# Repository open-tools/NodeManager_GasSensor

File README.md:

MySensors AirQuality board with eight MQ gas sensors, an MH-Z19 CO2 sensor and a Plantower PMSA003 PM25 particle sensor.

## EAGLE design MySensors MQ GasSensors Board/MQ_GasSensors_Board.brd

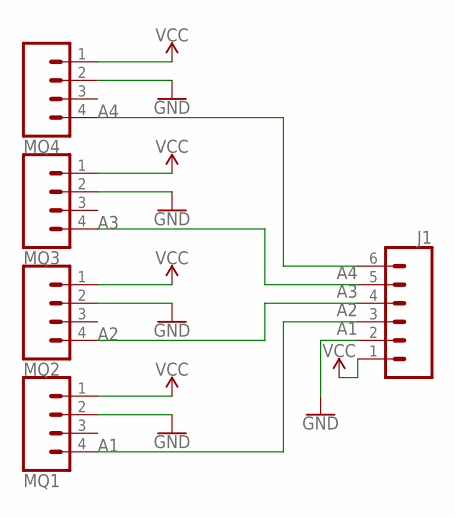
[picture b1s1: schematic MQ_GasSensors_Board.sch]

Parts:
J1: CONN_06SILK_FEMALE_PTH; 1X06
MQ1, MQ2, MQ3, MQ4: CONN_04; 1X04

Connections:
A1: J1.3, MQ1.4
A2: J1.4, MQ2.4
A3: J1.5, MQ3.4
A4: J1.6, MQ4.4
GND: J1.2, MQ1.2, MQ2.2, MQ3.2, MQ4.2
VCC: J1.1, MQ1.1, MQ2.1, MQ3.1, MQ4.1

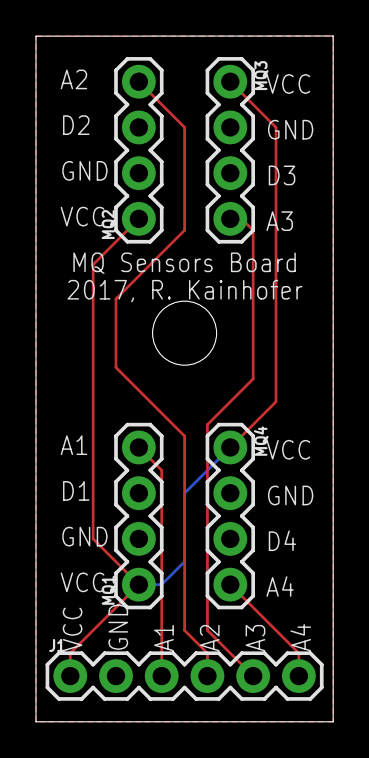
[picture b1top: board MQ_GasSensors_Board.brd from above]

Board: 2 copper layers, 16.5 x 38.1 mm, 5 parts (0 on the bottom side), 6 nets.

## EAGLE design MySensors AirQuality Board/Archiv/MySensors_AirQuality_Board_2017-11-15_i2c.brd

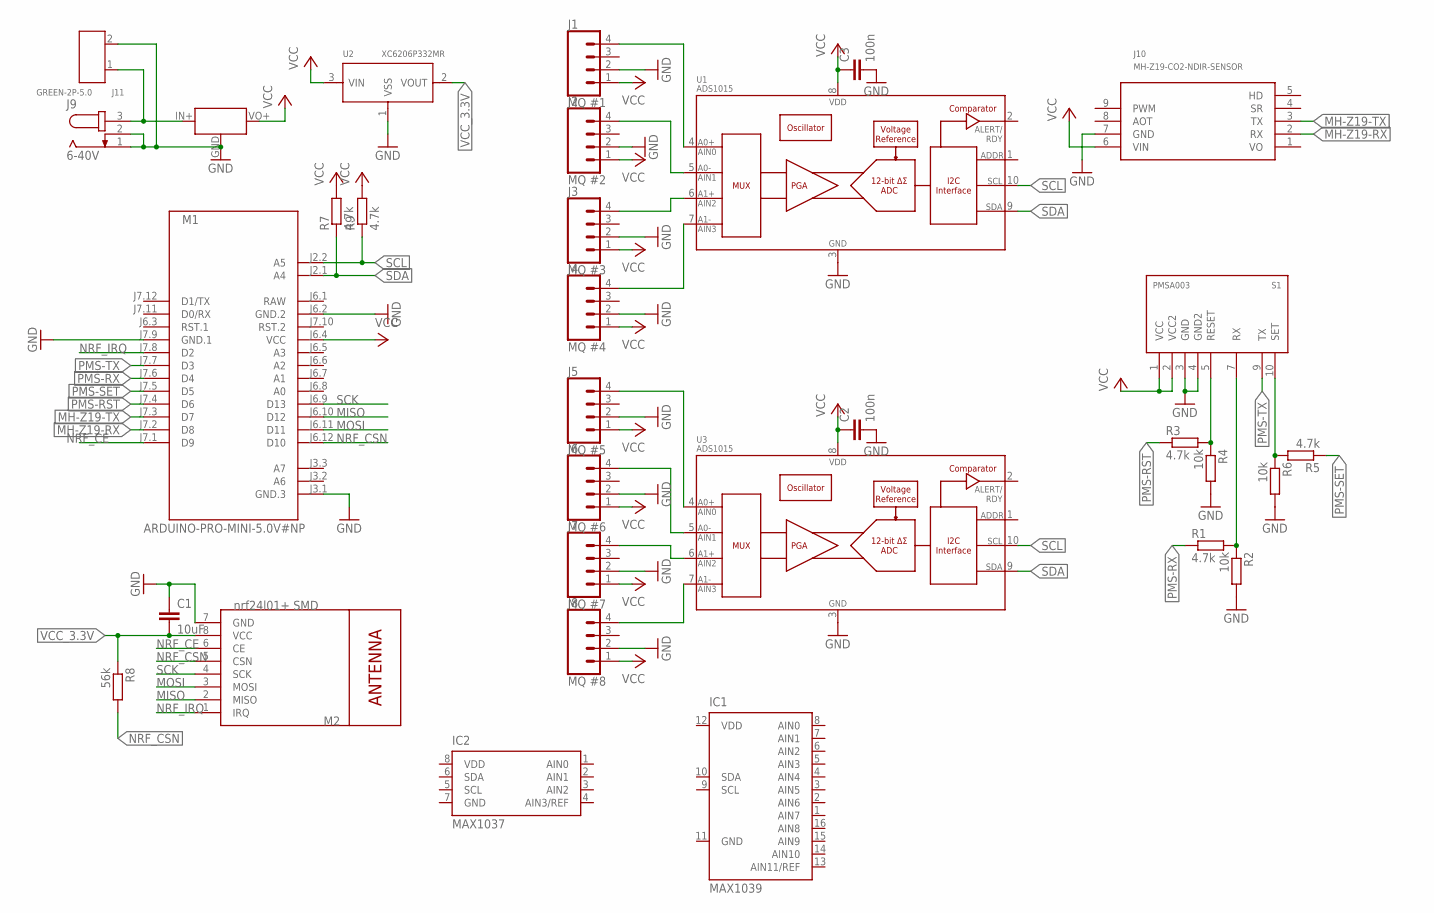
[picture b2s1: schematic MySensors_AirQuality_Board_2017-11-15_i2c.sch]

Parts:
C1: 10uF; C0805
C2, C3: 100n; C0805
IC1: MAX1039; QSOP16
IC2: MAX1037; SOT23-8L
J1: MQ #1; 1X04
J2: MQ #2; 1X04
J3: MQ #3; 1X04
J4: MQ #4; 1X04
J5: MQ #5; 1X04
J6: MQ #6; 1X04
J7: MQ #7; 1X04
J8: MQ #8; 1X04
J9: 6-40V; SPC4078
J10: MH-Z19-CO2-NDIR-SENSOR; MH-Z19
J11: GREEN-2P-5.0; H2-5.0-10.5X8.0MM
M1: ARDUINO-PRO-MINI-5.0V#NP; ARDUINO-PRO-MINI#NP
M2: nrf24l01+ SMD; WIRELESS-NRF24L01-SMD
R1, R3, R5, R7, R9: 4.7k; R0805
R2, R4, R6: 10k; R0805
R8: 56k; R0805
S1: PMSA003
U1, U3: ADS1015; MSOP10
U2: XC6206P332MR; SOT-23
U$2: MINI_BUCK_CONVERTER

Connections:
A0: J1.4, U1.4 (AIN0)
A1: J2.4, U1.5 (AIN1)
A2: J3.4, U1.6 (AIN2)
A3: J4.4, U1.7 (AIN3)
GND: C1.1, C2.2, C3.2, IC1.11 (GND), IC2.7 (GND), J1.2, J2.2, J3.2, J4.2, J5.2, J6.2, J7.2, J8.2, J9.1, J9.2, J10.7 (GND), J11.2, M1.J3.1 (GND.3), M1.J6.2 (GND.2), M1.J7.9 (GND.1), M2.7 (GND), R2.2, R4.2, R6.2, S1.3 (GND), S1.4 (GND2), U1.3 (VSS), U2.1 (VSS), U3.3 (VSS), U$2.GND
MH-Z19-RX: J10.2 (RX), M1.J7.2 (D8)
MH-Z19-TX: J10.3 (TX), M1.J7.3 (D7)
MISO: M1.J6.10 (D12), M2.2 (MISO)
MOSI: M1.J6.11 (D11), M2.3 (MOSI)
unnamed: J5.4, U3.4 (AIN0)
unnamed: J9.3, J11.1, U$2.IN+ (VIN)
unnamed: J6.4, U3.5 (AIN1)
unnamed: J7.4, U3.6 (AIN2)
unnamed: J8.4, U3.7 (AIN3)
NRF_CE: M1.J7.1 (D9), M2.6 (CE)
NRF_CSN: M1.J6.12 (D10), M2.5 (CSN), R8.2
NRF_IRQ: M1.J7.8 (D2), M2.1 (IRQ)
PMS-RESET-3.3V: R3.2, R4.1, S1.5 (RESET)
PMS-RST: M1.J7.4 (D6), R3.1
PMS-RX: M1.J7.6 (D4), R1.1
PMS-RX-3.3V: R1.2, R2.1, S1.7 (RX)
PMS-SET: M1.J7.5 (D5), R5.1
PMS-SET_3.3V: R5.2, R6.1, S1.10 (SET)
PMS-TX: M1.J7.7 (D3), S1.9 (TX)
RAW: M1.J6.1 (RAW)
SCK: M1.J6.9 (D13), M2.4 (SCK)
SCL: M1.J2.2 (A5), R9.1, U1.10 (SCL), U3.10 (SCL)
SDA: M1.J2.1 (A4), R7.1, U1.9 (SDA), U3.9 (SDA)
VCC: C2.1, C3.1, J1.1, J2.1, J3.1, J4.1, J5.1, J6.1, J7.1, J8.1, J10.6 (VIN), M1.J6.4 (VCC), R7.2, R9.2, S1.1 (VCC), S1.2 (VCC2), U1.8 (VDD), U2.3 (VIN), U3.8 (VDD), U$2.VO+ (VOUT)
VCC_3.3V: C1.2, M2.8 (VCC), R8.1, U2.2 (VOUT)
VDD: IC1.12 (VDD), IC2.8 (VDD)
VO: J10.1 (VO)

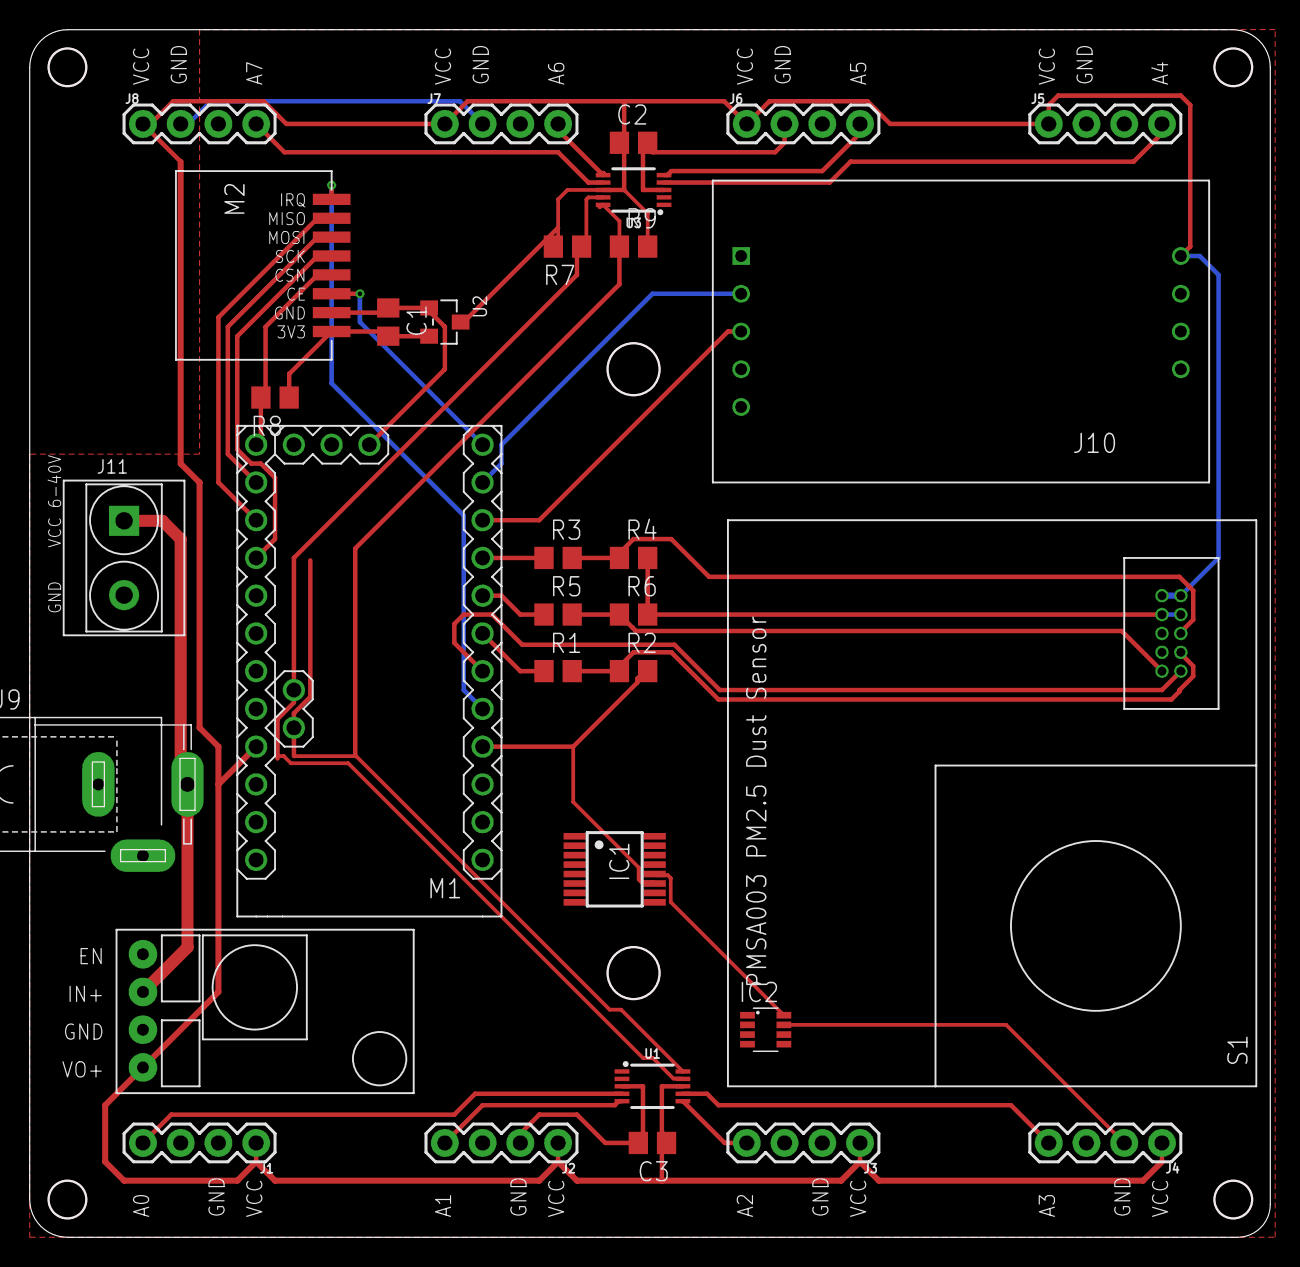
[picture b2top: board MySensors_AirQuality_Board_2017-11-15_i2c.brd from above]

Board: 2 copper layers, 83.3 x 81.1 mm, 32 parts (0 on the bottom side), 30 nets.

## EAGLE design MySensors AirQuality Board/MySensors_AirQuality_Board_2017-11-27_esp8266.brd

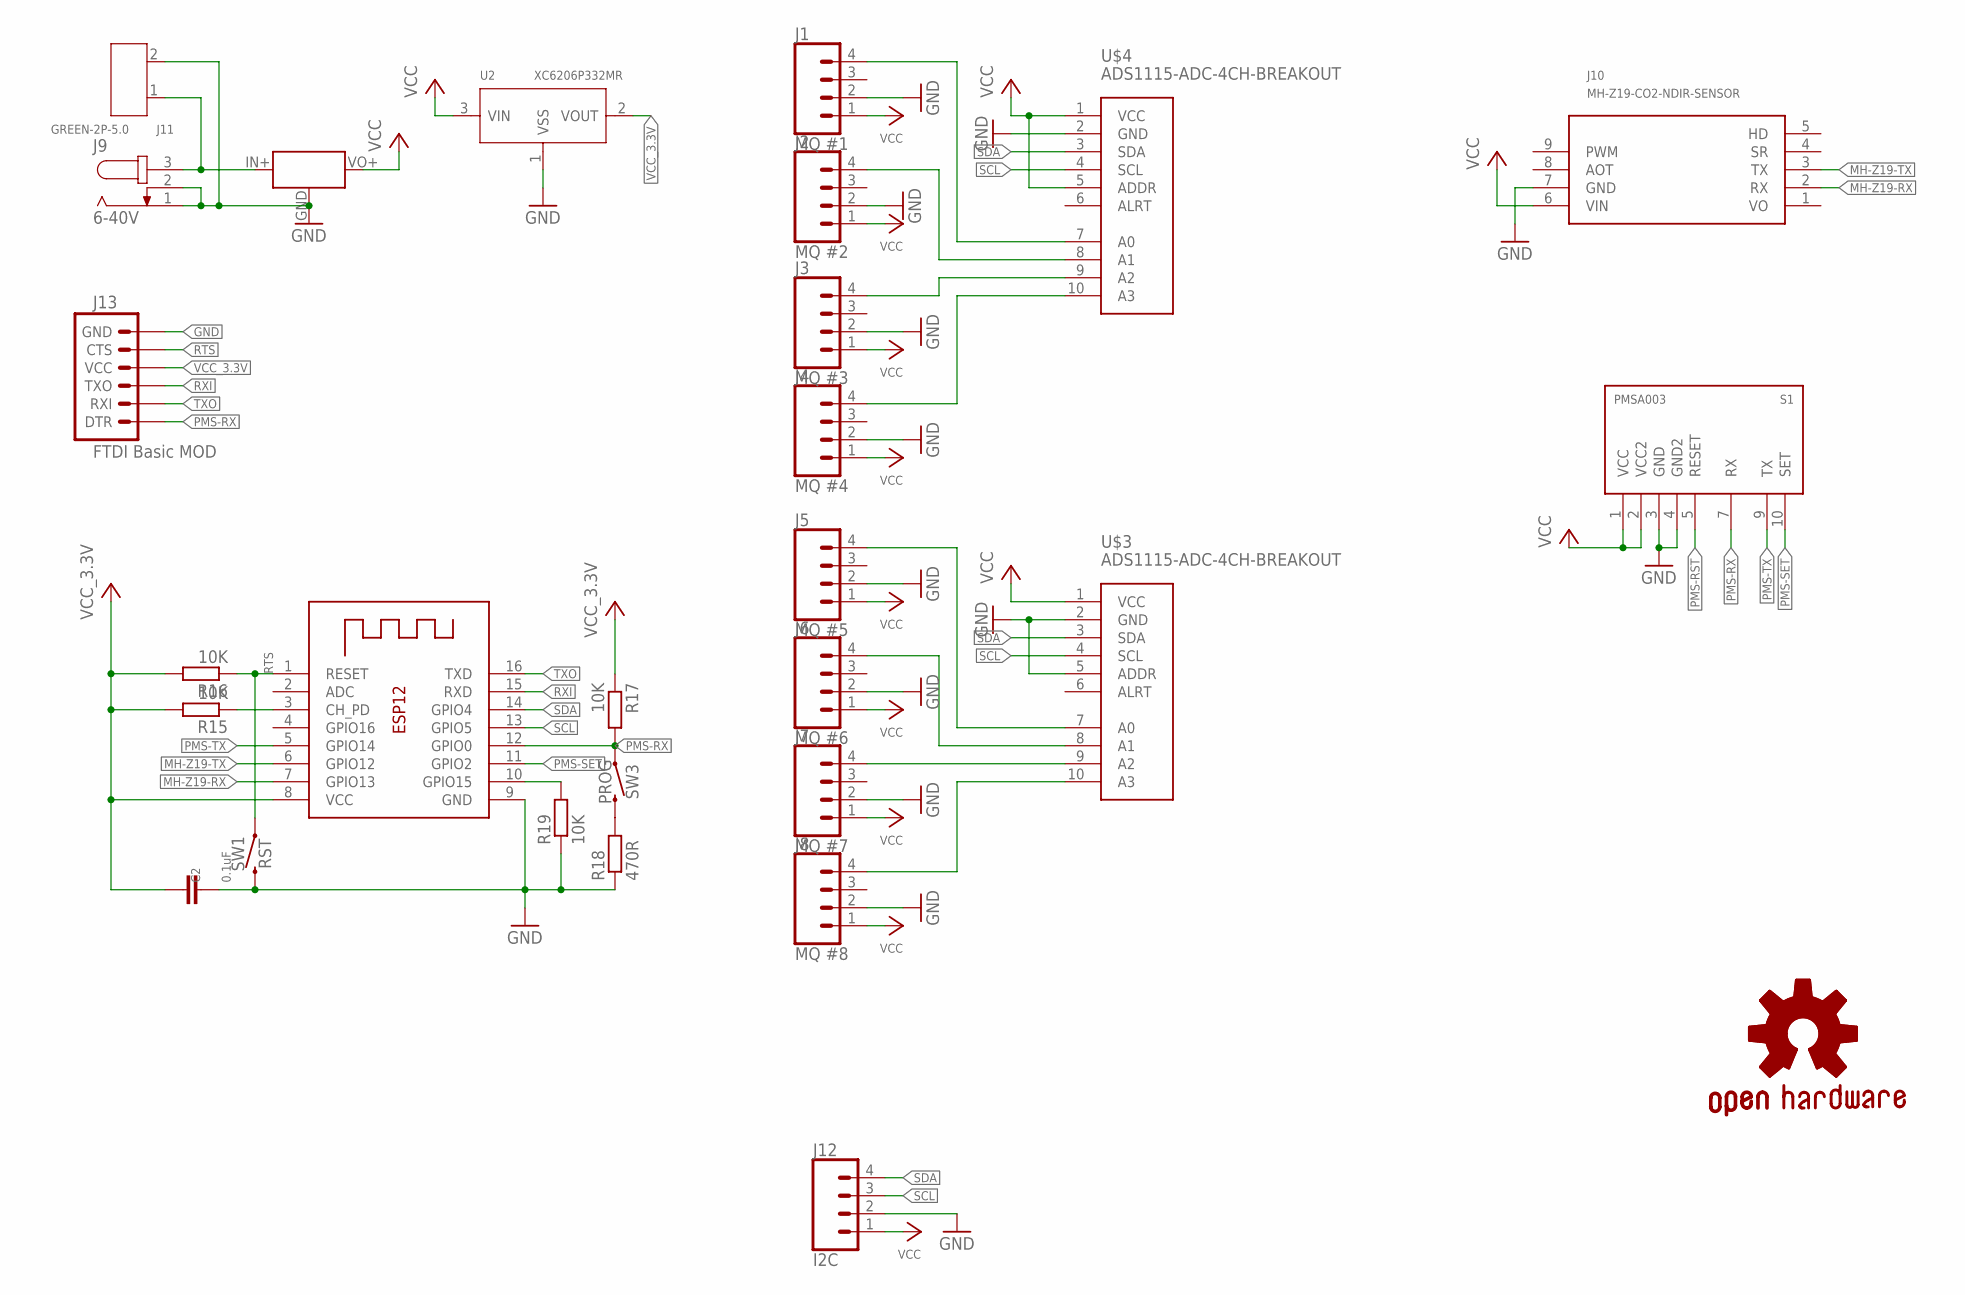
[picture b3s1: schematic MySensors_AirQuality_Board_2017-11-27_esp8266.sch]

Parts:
C2: 0.1uF; C0805
GOLD_ORB_SM1: OSHWLOGO_GOLD_ORB_SM; OSHW2
J1: MQ #1; 1X04
J2: MQ #2; 1X04
J3: MQ #3; 1X04
J4: MQ #4; 1X04
J5: MQ #5; 1X04
J6: MQ #6; 1X04
J7: MQ #7; 1X04
J8: MQ #8; 1X04
J9: 6-40V; SPC4078
J10: MH-Z19-CO2-NDIR-SENSOR; MH-Z19
J11: GREEN-2P-5.0; H2-5.0-10.5X8.0MM
J12: I2C; 1X04
J13: FTDI Basic MOD; 1X06
R15, R16, R17, R19: 10K; R0805
R18: 470R; R0805
S1: PMSA003
SW1: RST; TACTILE_SWITCH_SMD_6.0X3.5MM
SW3: PROG; TACTILE_SWITCH_SMD_6.0X3.5MM
U2: XC6206P332MR; SOT-23
U$2: MINI_BUCK_CONVERTER
U$3, U$4: ADS1115-ADC-4CH-BREAKOUT
X2: ESP-12e; ESP-12

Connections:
A0: J1.4, U$4.7 (A0)
A1: J2.4, U$4.8 (A1)
A2: J3.4, U$4.9 (A2)
A3: J4.4, U$4.10 (A3)
CH_PD: R15.1, X2.3 (CH_PD)
GND: C2.1, J1.2, J2.2, J3.2, J4.2, J5.2, J6.2, J7.2, J8.2, J9.1, J9.2, J10.7 (GND), J11.2, J12.2, J13.6 (GND), R18.1, R19.1, S1.3 (GND), S1.4 (GND2), SW1.2, U2.1 (VSS), U$2.GND, U$3.2 (GND), U$3.5 (ADDR), U$4.2 (GND), X2.9 (GND)
GPIO15: R19.2, X2.10 (GPIO15)
MH-Z19-RX: J10.2 (RX), X2.7 (GPIO13)
MH-Z19-TX: J10.3 (TX), X2.6 (GPIO12)
unnamed: J5.4, U$3.7 (A0)
unnamed: J9.3, J11.1, U$2.IN+ (VIN)
unnamed: J6.4, U$3.8 (A1)
unnamed: J7.4, U$3.9 (A2)
unnamed: J8.4, U$3.10 (A3)
unnamed: R18.2, SW3.2
PMS-RST: S1.5 (RESET)
PMS-RX: J13.1 (DTR), R17.2, S1.7 (RX), SW3.1, X2.12 (GPIO0)
PMS-SET: S1.10 (SET), X2.11 (GPIO2)
PMS-TX: S1.9 (TX), X2.5 (GPIO14)
RTS: J13.5 (CTS), R16.1, SW1.1, X2.1 (RESET)
RXI: J13.3 (TXO), X2.15 (RXD)
SCL: J12.3, U$3.4 (SCL), U$4.4 (SCL), X2.13 (GPIO5)
SDA: J12.4, U$3.3 (SDA), U$4.3 (SDA), X2.14 (GPIO4)
TXO: J13.2 (RXI), X2.16 (TXD)
VCC: J1.1, J2.1, J3.1, J4.1, J5.1, J6.1, J7.1, J8.1, J10.6 (VIN), J12.1, S1.1 (VCC), S1.2 (VCC2), U2.3 (VIN), U$2.VO+ (VOUT), U$3.1 (VCC), U$4.1 (VCC), U$4.5 (ADDR)
VCC_3.3V: C2.2, J13.4 (VCC), R15.2, R16.2, R17.1, U2.2 (VOUT), X2.8 (VCC)
VO: J10.1 (VO)

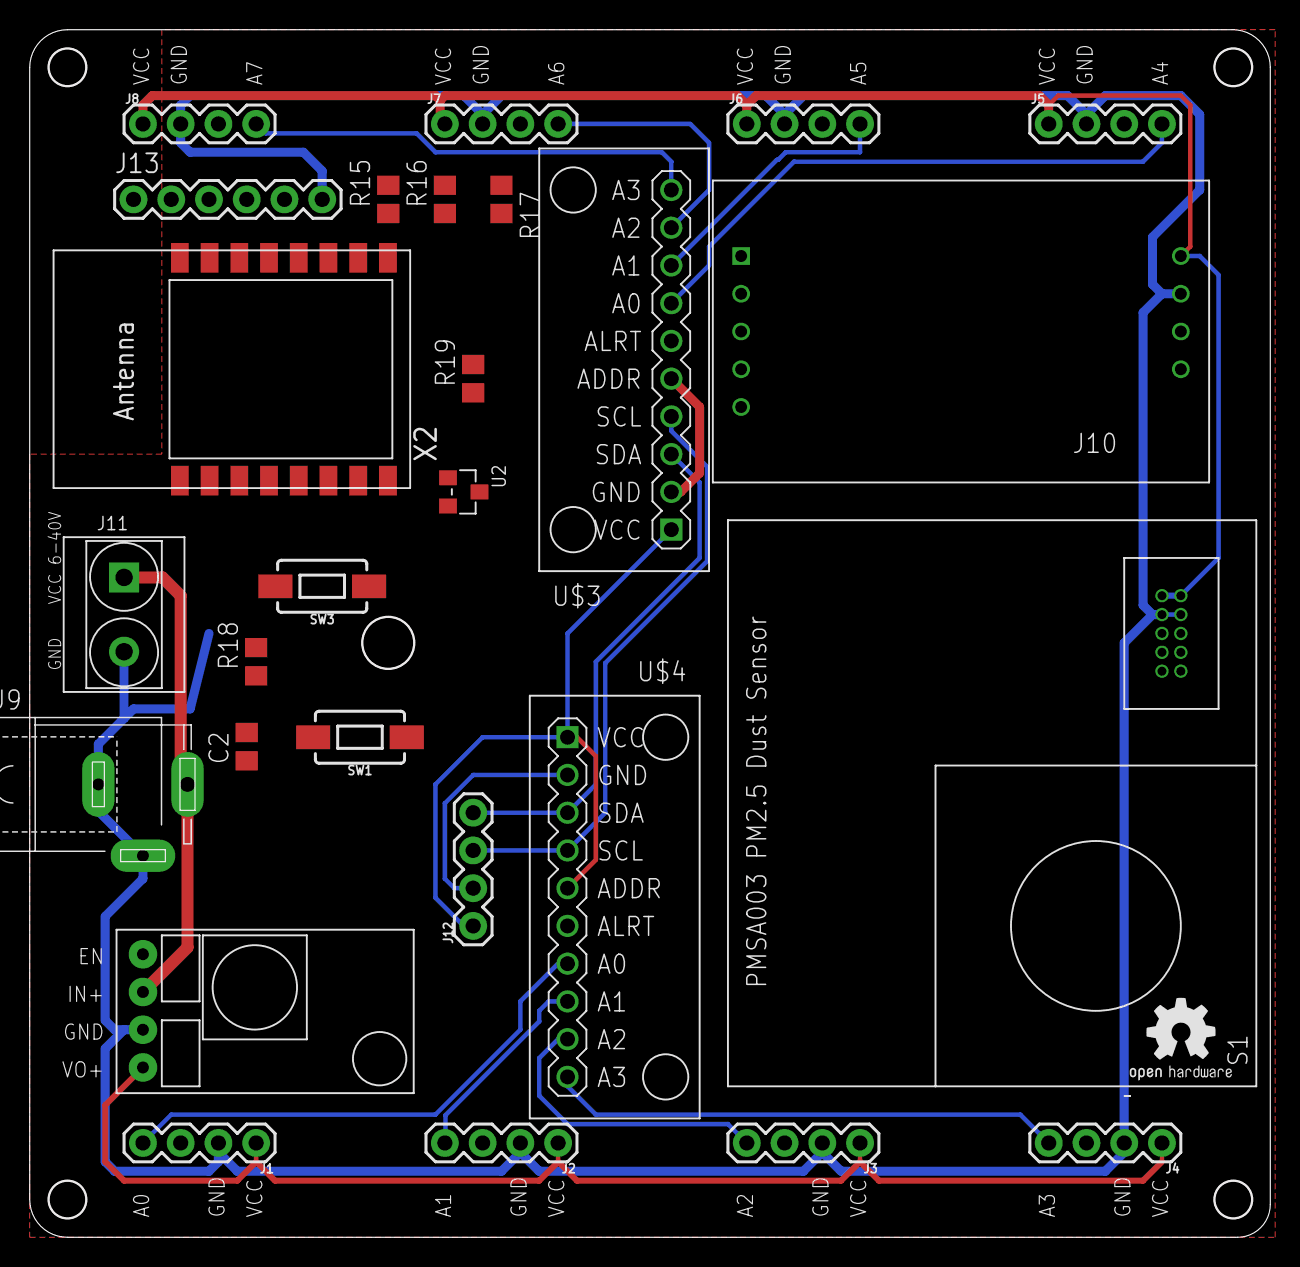
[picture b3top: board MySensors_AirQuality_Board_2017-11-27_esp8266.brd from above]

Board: 2 copper layers, 83.3 x 81.1 mm, 28 parts (0 on the bottom side), 25 nets.

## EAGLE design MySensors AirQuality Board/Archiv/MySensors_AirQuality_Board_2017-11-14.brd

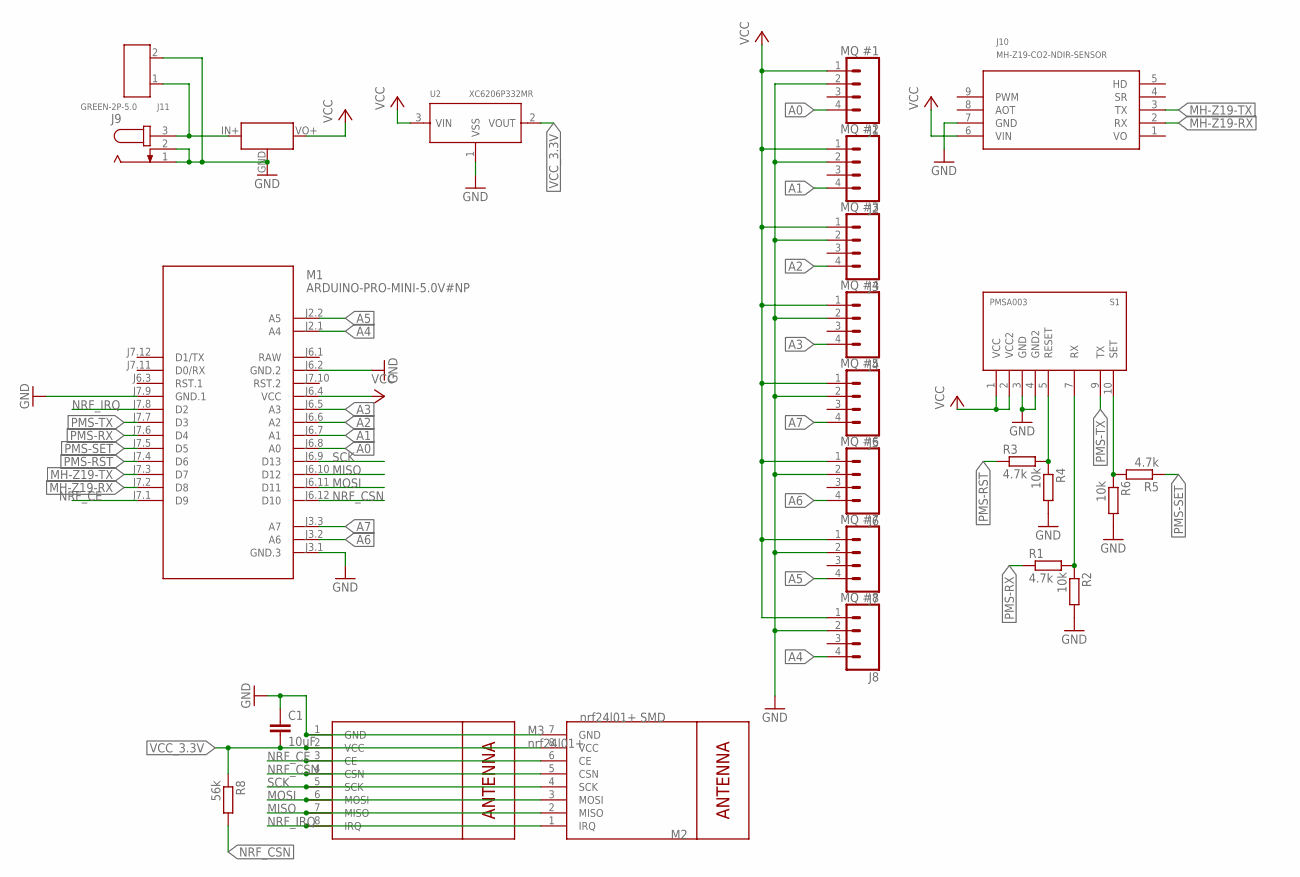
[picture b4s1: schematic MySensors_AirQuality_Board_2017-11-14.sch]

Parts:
C1: 10uF; C0805
J1: MQ #1; 1X04
J2: MQ #2; 1X04
J3: MQ #3; 1X04
J4: MQ #4; 1X04
J5: MQ #5; 1X04
J6: MQ #6; 1X04
J7: MQ #7; 1X04
J8: MQ #8; 1X04
J9: JACK-PLUG1; SPC4078
J10: MH-Z19-CO2-NDIR-SENSOR; MH-Z19
J11: GREEN-2P-5.0; H2-5.0-10.5X8.0MM
M1: ARDUINO-PRO-MINI-5.0V#NP; ARDUINO-PRO-MINI#NP
M2: nrf24l01+ SMD; WIRELESS-NRF24L01-SMD
M3: nrf24l01+; WIRELESS-NRF24L01
R1, R3, R5: 4.7k; R0805
R2, R4, R6: 10k; R0805
R8: 56k; R0805
S1: PMSA003
U2: XC6206P332MR; SOT-23
U$2: MINI_BUCK_CONVERTER

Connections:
A0: J1.4, M1.J6.8 (A0)
A1: J2.4, M1.J6.7 (A1)
A2: J3.4, M1.J6.6 (A2)
A3: J4.4, M1.J6.5 (A3)
A4: J8.4, M1.J2.1 (A4)
A5: J7.4, M1.J2.2 (A5)
A6: J6.4, M1.J3.2 (A6)
A7: J5.4, M1.J3.3 (A7)
GND: C1.1, J1.2, J2.2, J3.2, J4.2, J5.2, J6.2, J7.2, J8.2, J9.1, J9.2, J10.7 (GND), J11.2, M1.J3.1 (GND.3), M1.J6.2 (GND.2), M1.J7.9 (GND.1), M2.7 (GND), M3.1 (GND), R2.2, R4.2, R6.2, S1.3 (GND), S1.4 (GND2), U2.1 (VSS), U$2.GND
MH-Z19-RX: J10.2 (RX), M1.J7.2 (D8)
MH-Z19-TX: J10.3 (TX), M1.J7.3 (D7)
MISO: M1.J6.10 (D12), M2.2 (MISO), M3.7 (MISO)
MOSI: M1.J6.11 (D11), M2.3 (MOSI), M3.6 (MOSI)
unnamed: J9.3, J11.1, U$2.IN+ (VIN)
NRF_CE: M1.J7.1 (D9), M2.6 (CE), M3.3 (CE)
NRF_CSN: M1.J6.12 (D10), M2.5 (CSN), M3.4 (CSN), R8.2
NRF_IRQ: M1.J7.8 (D2), M2.1 (IRQ), M3.8 (IRQ)
PMS-RESET-3.3V: R3.2, R4.1, S1.5 (RESET)
PMS-RST: M1.J7.4 (D6), R3.1
PMS-RX: M1.J7.6 (D4), R1.1
PMS-RX-3.3V: R1.2, R2.1, S1.7 (RX)
PMS-SET: M1.J7.5 (D5), R5.1
PMS-SET_3.3V: R5.2, R6.1, S1.10 (SET)
PMS-TX: M1.J7.7 (D3), S1.9 (TX)
RAW: M1.J6.1 (RAW)
SCK: M1.J6.9 (D13), M2.4 (SCK), M3.5 (SCK)
VCC: J1.1, J2.1, J3.1, J4.1, J5.1, J6.1, J7.1, J8.1, J10.6 (VIN), M1.J6.4 (VCC), S1.1 (VCC), S1.2 (VCC2), U2.3 (VIN), U$2.VO+ (VOUT)
VCC_3.3V: C1.2, M2.8 (VCC), M3.2 (VCC), R8.1, U2.2 (VOUT)
VO: J10.1 (VO)

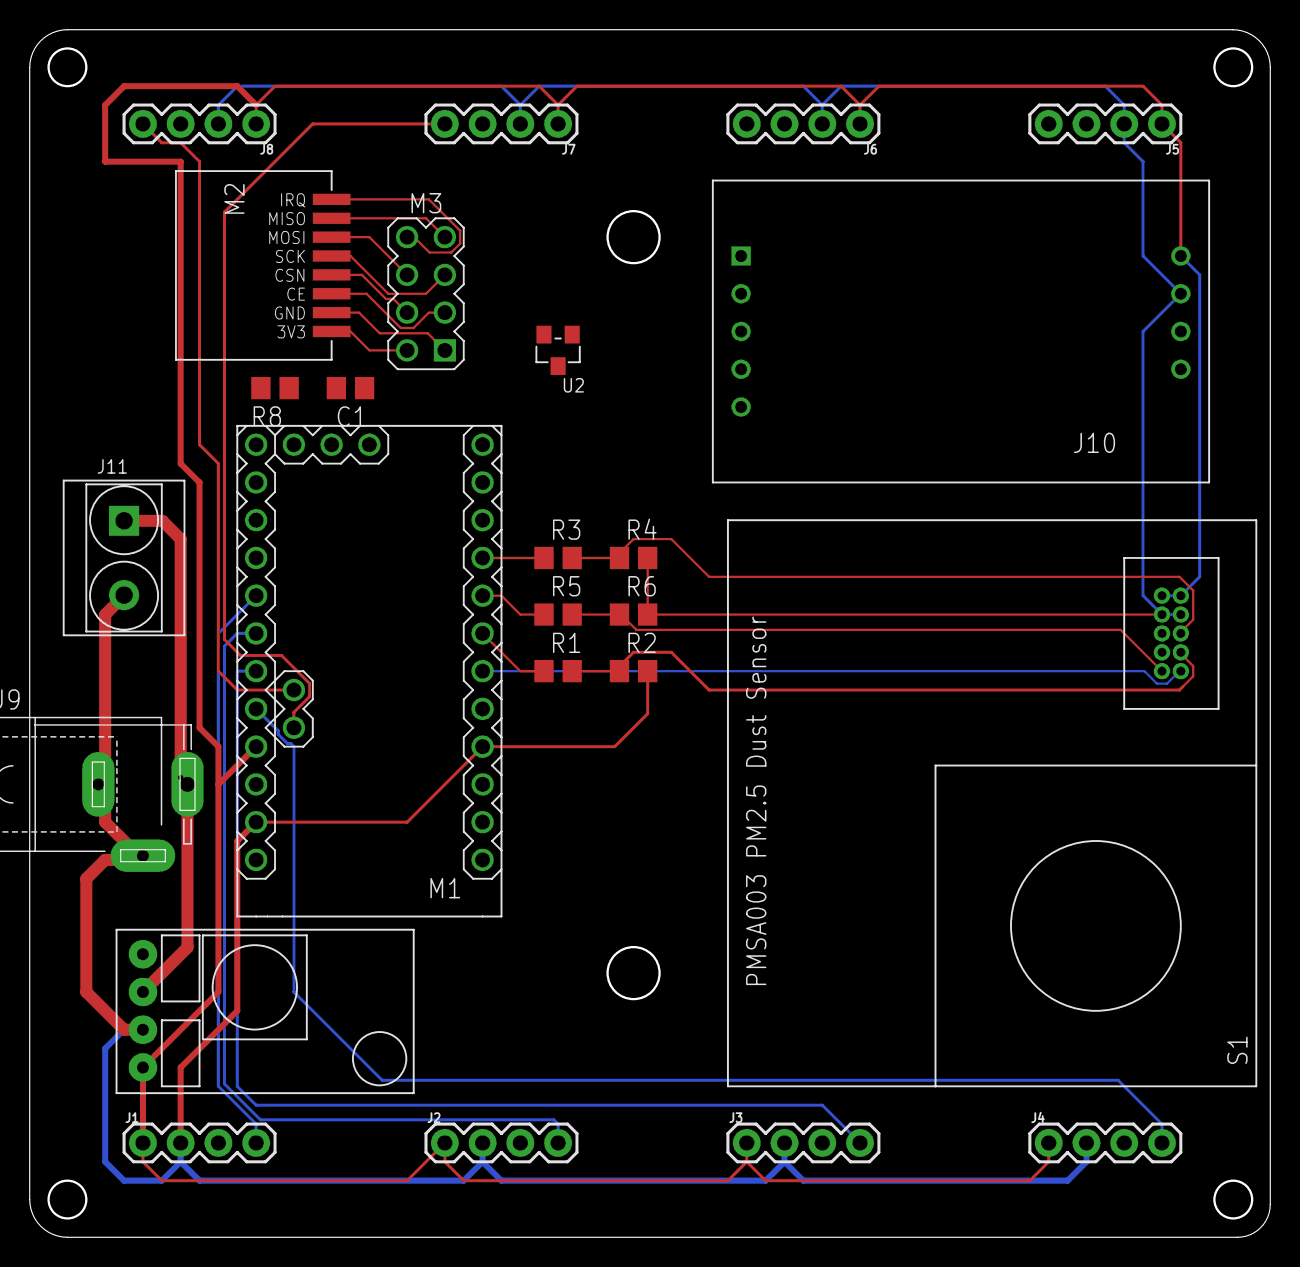
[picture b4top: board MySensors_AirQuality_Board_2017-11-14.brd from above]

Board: 2 copper layers, 83.3 x 81.1 mm, 25 parts (0 on the bottom side), 27 nets.

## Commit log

2017-07-25 Add debug statements printing out free memory
2017-07-25 Ignore the origina NodeManager.ino (otherwise we'll have error messages about duplicate inclusions)
2017-07-25 Adjust the config for our GasSensor configuration
2017-10-29 DEBUG: Add printout about current free memory
2017-10-30 Update for PlatformIO
2017-10-30 Update to new NodeManager API
2017-10-30 Update with changes from latest NM 1.7-dev
2017-12-09 Add PCBs
2017-12-09 Add hole to MQ sensors board; generate Gerbers
2017-12-26 Add image of working board

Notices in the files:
MySensors AirQuality Board/Archiv/MySensors_AirQuality_Board_2017-11-15_i2c.brd:
Licensed under the CERN OHL v1.2
parts and their libraries:
SparkFun-Connectors: Licensing: Creative Commons ShareAlike 4.0 International - https://creativecommons.org/licenses/by-sa/4.0
diy-modules: Released under the Creative Commons Attribution 4.0 International License: http://creativecommons.org/licenses/by/4.0
